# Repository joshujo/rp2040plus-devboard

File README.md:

# RP2040+ Devboard

This is a devboard that is designed to have a basic sensor, OLED screen, buttons and LEDs pre-embedded onto the board. The idea of this design was to have some basic hardware already available on the development board itself so an external bread board and some additional components with a kit and such is not needed to use it. Additionally, it can be used as a simple console or just a temperature monitor if desired. The board is designed to be extended with an additional 17 GPIO pins exposed to the user for prototyping. 

## Features

- 17 GPIO pins exposed
- HDC1080 accurate temperature + humidity sensor
- Buzzer
- OLED screen
- USB-C connector for power + data
- An additional power only USB-C connector designed to have an external battery plugged in
- 10 NeoPixel LEDs
- Programmable matrix buttons
- Up to 900mA +3V3
- Up to 3A VBUS
- 13 programmable buttons
- Designed to be used as is, no external bread board or components needed
- Moderate form factor of 100x40mm
- RP2040 comes with another I²C bus for more external components

# Datasheet

## Base
HDC1080 Addr: 1000000\
OLED Addr: 0111100 or 0111101\
Buzzer: GPIO24\
LED: GPIO25\
Neopixels: GPIO14

## Keypad
Shift: GPIO13\
ROW0: GPIO15\
ROW1: GPIO16\
ROW2: GPIO17\
ROW3: GPIO18\
COL0: GPIO19\
COL1: GPIO20\
COL2: GPIO21

## I²C
SDA: GPIO22\
SCL: GPIO23

# Schematic

# PCB

# BOM

| Item                     | Description                                                                                                                   | Quantity(For 5 units at minimum order amount) | Unit Price | Total Price | URL                                                                                                      | Running Total |
| ------------------------ | ----------------------------------------------------------------------------------------------------------------------------- | --------------------------------------------- | ---------- | ----------- | -------------------------------------------------------------------------------------------------------- | ------------- |
| CL05A105KP5NNNC          | 10V 1uF X5R ±10% 0402 Ceramic Capacitors RoHS                                                                                 | 100                                           | 0.0017     | $0.17       | [https://www.lcsc.com/product-detail/C14445.html](https://www.lcsc.com/product-detail/C14445.html)       | $0.17         |
| CL05B104KO5NNNC          | 16V 100nF X7R ±10% 0402 Ceramic Capacitors RoHS                                                                               | 100                                           | 0.0012     | $0.12       | [https://www.lcsc.com/product-detail/C1525.html](https://www.lcsc.com/product-detail/C1525.html)         | $0.29         |
| CC0603JRNPO9BN330        | 50V 33pF NP0 ±5% 0603 Ceramic Capacitors RoHS                                                                                 | 100                                           | 0.0024     | $0.24       | [https://www.lcsc.com/product-detail/C107047.html](https://www.lcsc.com/product-detail/C107047.html)     | $0.53         |
| CL10B104KB8NNNC          | 50V 100nF X7R ±10% 0603 Ceramic Capacitors RoHS                                                                               | 100                                           | 0.0026     | $0.26       | [https://www.lcsc.com/product-detail/C1591.html](https://www.lcsc.com/product-detail/C1591.html)         | $0.79         |
| CL10A106KP8NNNC          | 10V 10uF X5R ±10% 0603 Ceramic Capacitors RoHS                                                                                | 50                                            | 0.0058     | $0.29       | [https://www.lcsc.com/product-detail/C19702.html](https://www.lcsc.com/product-detail/C19702.html)       | $1.08         |
| CL10A105KB8NNNC          | 50V 1uF X5R ±10% 0603 Ceramic Capacitors RoHS                                                                                 | 50                                            | 0.0049     | $0.25       | [https://www.lcsc.com/product-detail/C15849.html](https://www.lcsc.com/product-detail/C15849.html)       | $1.33         |
| CL31A107MQHNNNE          | 6.3V 100uF X5R ±20% 1206 Ceramic Capacitors RoHS                                                                              | 20                                            | 0.0552     | $1.10       | [https://www.lcsc.com/product-detail/C15008.html](https://www.lcsc.com/product-detail/C15008.html)       | $2.43         |
| KT-0805B                 | 5mA 100mcd 460nm~475nm Blue 100mW 3.1V 0805 LED Indication - Discrete RoHS                                                    | 50                                            | 0.0117     | $0.59       | [https://www.lcsc.com/product-detail/C2293.html](https://www.lcsc.com/product-detail/C2293.html)         | $3.02         |
| CD4148WSP                | 1A 4ns Independent 75V 1.25V@100mA 150mA 0805 Single Diodes RoHS                                                              | 100                                           | 0.0118     | $1.18       | [https://www.lcsc.com/product-detail/C30584799.html](https://www.lcsc.com/product-detail/C30584799.html) | $4.20         |
| WS2812B-2020             | SMD,2.2x2mm LED Addressable, Specialty RoHS                                                                                   | 60                                            | 0.0658     | $3.95       | [https://www.lcsc.com/product-detail/C965555.html](https://www.lcsc.com/product-detail/C965555.html)     | $8.15         |
| TYPE-C-31-M-12           | 1 16P Type-C SMD USB, DVI, HDMI Connector Assemblies RoHS                                                                     | 5                                             | 0.1762     | $0.88       | [https://www.lcsc.com/product-detail/C165948.html](https://www.lcsc.com/product-detail/C165948.html)     | $9.03         |
| SKTDLHE010               | Without Bracket Rectangular Button No 3.9mm SPST SMD Tactile Switches RoHS                                                    | 10                                            | 0.1646     | $1.65       | [https://www.lcsc.com/product-detail/C380198.html](https://www.lcsc.com/product-detail/C380198.html)     | $10.68        |
| SKSLLBE010               | 12V 2.2mm Round Button No 4.5mm SPST 50mA SMD,4.5x2.2mm Tactile Switches RoHS                                                 | 65                                            | 0.159      | $10.34      | [https://www.lcsc.com/product-detail/C358617.html](https://www.lcsc.com/product-detail/C358617.html)     | $21.02        |
| RP2040                   | 133MHz 30 LQFN-56(7x7) Microcontrollers RoHS                                                                                  | 3                                             | 0.9482     | $2.84       | [https://www.lcsc.com/product-detail/C2040.html](https://www.lcsc.com/product-detail/C2040.html)         | $23.86        |
| HDC1080DMBR              | ±2%RH -40℃~+125℃ 0%RH~100%RH I2C WSON-6(3x3) Humidity, Moisture Sensors RoHS                                                  | 5                                             | 0.9001     | $4.50       | [https://www.lcsc.com/product-detail/C82227.html](https://www.lcsc.com/product-detail/C82227.html)       | $28.36        |
| NX3225GA-12MHZ-STD-CRG-2 | 8pF SMD3225-4P Crystals RoHS                                                                                                  | 5                                             | 0.257      | $1.29       | [https://www.lcsc.com/product-detail/C481407.html](https://www.lcsc.com/product-detail/C481407.html)     | $29.65        |
| MLT-8530                 | 80dB Passive (Externally Driven) 2.7kHz 3.6V Electromagnetic SMD,8.5x8.5mm Alarms, Buzzers, and Sirens RoHS                   | 5                                             | 0.1941     | $0.97       | [https://www.lcsc.com/product-detail/C94599.html](https://www.lcsc.com/product-detail/C94599.html)       | $30.62        |
| TPS2116DRLR              | 2 Active High 2.5A SOT-583 Power Distribution Switches, Load Drivers RoHS                                                     | 5                                             | 0.3756     | $1.88       | [https://www.lcsc.com/product-detail/C3235557.html](https://www.lcsc.com/product-detail/C3235557.html)   | $32.50        |
| HS96L03W2C03             | 0.96 128x64 SSD1315 I2C LCD, OLED, Graphic RoHS                                                                               | 5                                             | 2.0084     | $10.04      | [https://www.lcsc.com/product-detail/C5248080.html](https://www.lcsc.com/product-detail/C5248080.html)   | $42.54        |
| W25Q128JVSIQ             | 128Mbit 2.7V~3.6V 133MHz SPI SOIC-8-208mil Memory (ICs) RoHS                                                                  | 5                                             | 1.5657     | $7.83       | [https://www.lcsc.com/product-detail/C97521.html](https://www.lcsc.com/product-detail/C97521.html)       | $50.37        |
| NCP1117ST33T3G           | 62dB@(120Hz) Positive Fixed 3.3V SOT-223 Voltage Regulators - Linear, Low Drop Out (LDO) Regulators RoHS                      | 5                                             | 0.2315     | $1.16       | [https://www.lcsc.com/product-detail/C26537.html](https://www.lcsc.com/product-detail/C26537.html)       | $51.53        |
| BSS138LT1G               | 50V 200mA 225mW 5.6Ω@2.75V One N-channel SOT-23 Single FETs, MOSFETs RoHS                                                     | 20                                            | 0.0342     | $0.68       | [https://www.lcsc.com/product-detail/C82045.html](https://www.lcsc.com/product-detail/C82045.html)       | $52.21        |
| FRC0603F27R4TS           | 100mW 27.4Ω 75V ±100ppm/℃ Thick Film Resistor ±1% 0603 Chip Resistor - Surface Mount RoHS                                     | 100                                           | 0.0009     | $0.09       | [https://www.lcsc.com/product-detail/C5126244.html](https://www.lcsc.com/product-detail/C5126244.html)   | $52.30        |
| 0603WAF4700T5E           | 100mW 470Ω 75V ±100ppm/℃ Thick Film Resistor ±1% 0603 Chip Resistor - Surface Mount RoHS                                      | 100                                           | 0.0012     | $0.12       | [https://www.lcsc.com/product-detail/C23179.html](https://www.lcsc.com/product-detail/C23179.html)       | $52.42        |
| AR03BTCX5001             | 100mW 5kΩ 75V ±25ppm/℃ Thin Film Resistor ±0.1% 0603 Chip Resistor - Surface Mount RoHS                                       | 20                                            | 0.0302     | $0.60       | [https://www.lcsc.com/product-detail/C2828621.html](https://www.lcsc.com/product-detail/C2828621.html)   | $53.02        |
| RC0603FR-07100RL         | 100mW 100Ω 75V ±100ppm/℃ Thick Film Resistor ±1% 0603 Chip Resistor - Surface Mount RoHS                                      | 100                                           | 0.0011     | $0.11       | [https://www.lcsc.com/product-detail/C105588.html](https://www.lcsc.com/product-detail/C105588.html)     | $53.13        |
| FRC0603F5101TS           | 100mW 5.1kΩ 75V ±100ppm/℃ Thick Film Resistor ±1% 0603 Chip Resistor - Surface Mount RoHS                                     | 100                                           | 0.0009     | $0.09       | [https://www.lcsc.com/product-detail/C2907044.html](https://www.lcsc.com/product-detail/C2907044.html)   | $53.22        |
| RC0603FR-0710KL          | 100mW 10kΩ 75V ±100ppm/℃ Thick Film Resistor ±1% 0603 Chip Resistor - Surface Mount RoHS                                      | 100                                           | 0.0011     | $0.11       | [https://www.lcsc.com/product-detail/C98220.html](https://www.lcsc.com/product-detail/C98220.html)       | $53.33        |
| FRC0603F3302TS           | 33kΩ 100mW 75V ±100ppm/℃ Thick Film Resistor ±1% 0603 Chip Resistor - Surface Mount RoHS                                      | 100                                           | 0.0009     | $0.09       | [https://www.lcsc.com/product-detail/C2907028.html](https://www.lcsc.com/product-detail/C2907028.html)   | $53.42        |
| PZ254V-11-03P            | 3P 1x3P -40℃~+105℃ Pin Header Black 2.54mm 2.5mm 6mm 250V 3mm 1 3A Through Hole Through Hole,P=2.54mm Headers, Male Pins RoHS | 50                                            | 0.0162     | $0.81       | [https://www.lcsc.com/product-detail/C2937625.html](https://www.lcsc.com/product-detail/C2937625.html)   | $54.23        |
| PZ254V-11-04P            | 4P 1x4P -40℃~+105℃ Black Pin Header 2.54mm 2.5mm 6mm 250V 3mm 1 3A Through Hole Through Hole,P=2.54mm Headers, Male Pins RoHS | 20                                            | 0.0217     | $0.43       | [https://www.lcsc.com/product-detail/C2691448.html](https://www.lcsc.com/product-detail/C2691448.html)   | $54.66        |
| 0402WGF1001TCE           | 1kΩ 62.5mW 50V ±100ppm/℃ Thick Film Resistor ±1% 0402 Chip Resistor - Surface Mount RoHS                                      | 100                                           | 0.0006     | $0.06       | [https://www.lcsc.com/product-detail/C11702.html](https://www.lcsc.com/product-detail/C11702.html)       | $54.72        |
| KT-0805G                 | 5mA 430mcd 513nm\~528nm Emerald Green 100mW 2.6V\~3.1V 0805 LED Indication - Discrete RoHS                                      | 50                                            | 0.0112     | $0.56       | [https://www.lcsc.com/product-detail/C2297.html](https://www.lcsc.com/product-detail/C2297.html)         | $55.28        |
| TYPE-C 6P(073)           | 1 6P -25℃~+85℃ Type-C SMD USB, DVI, HDMI Connector Assemblies RoHS                                                            | 10                                            | 0.0357     | $0.36       | [https://www.lcsc.com/product-detail/C668623.html](https://www.lcsc.com/product-detail/C668623.html)     | $55.64        |

Plus $31.36 for the PCBs

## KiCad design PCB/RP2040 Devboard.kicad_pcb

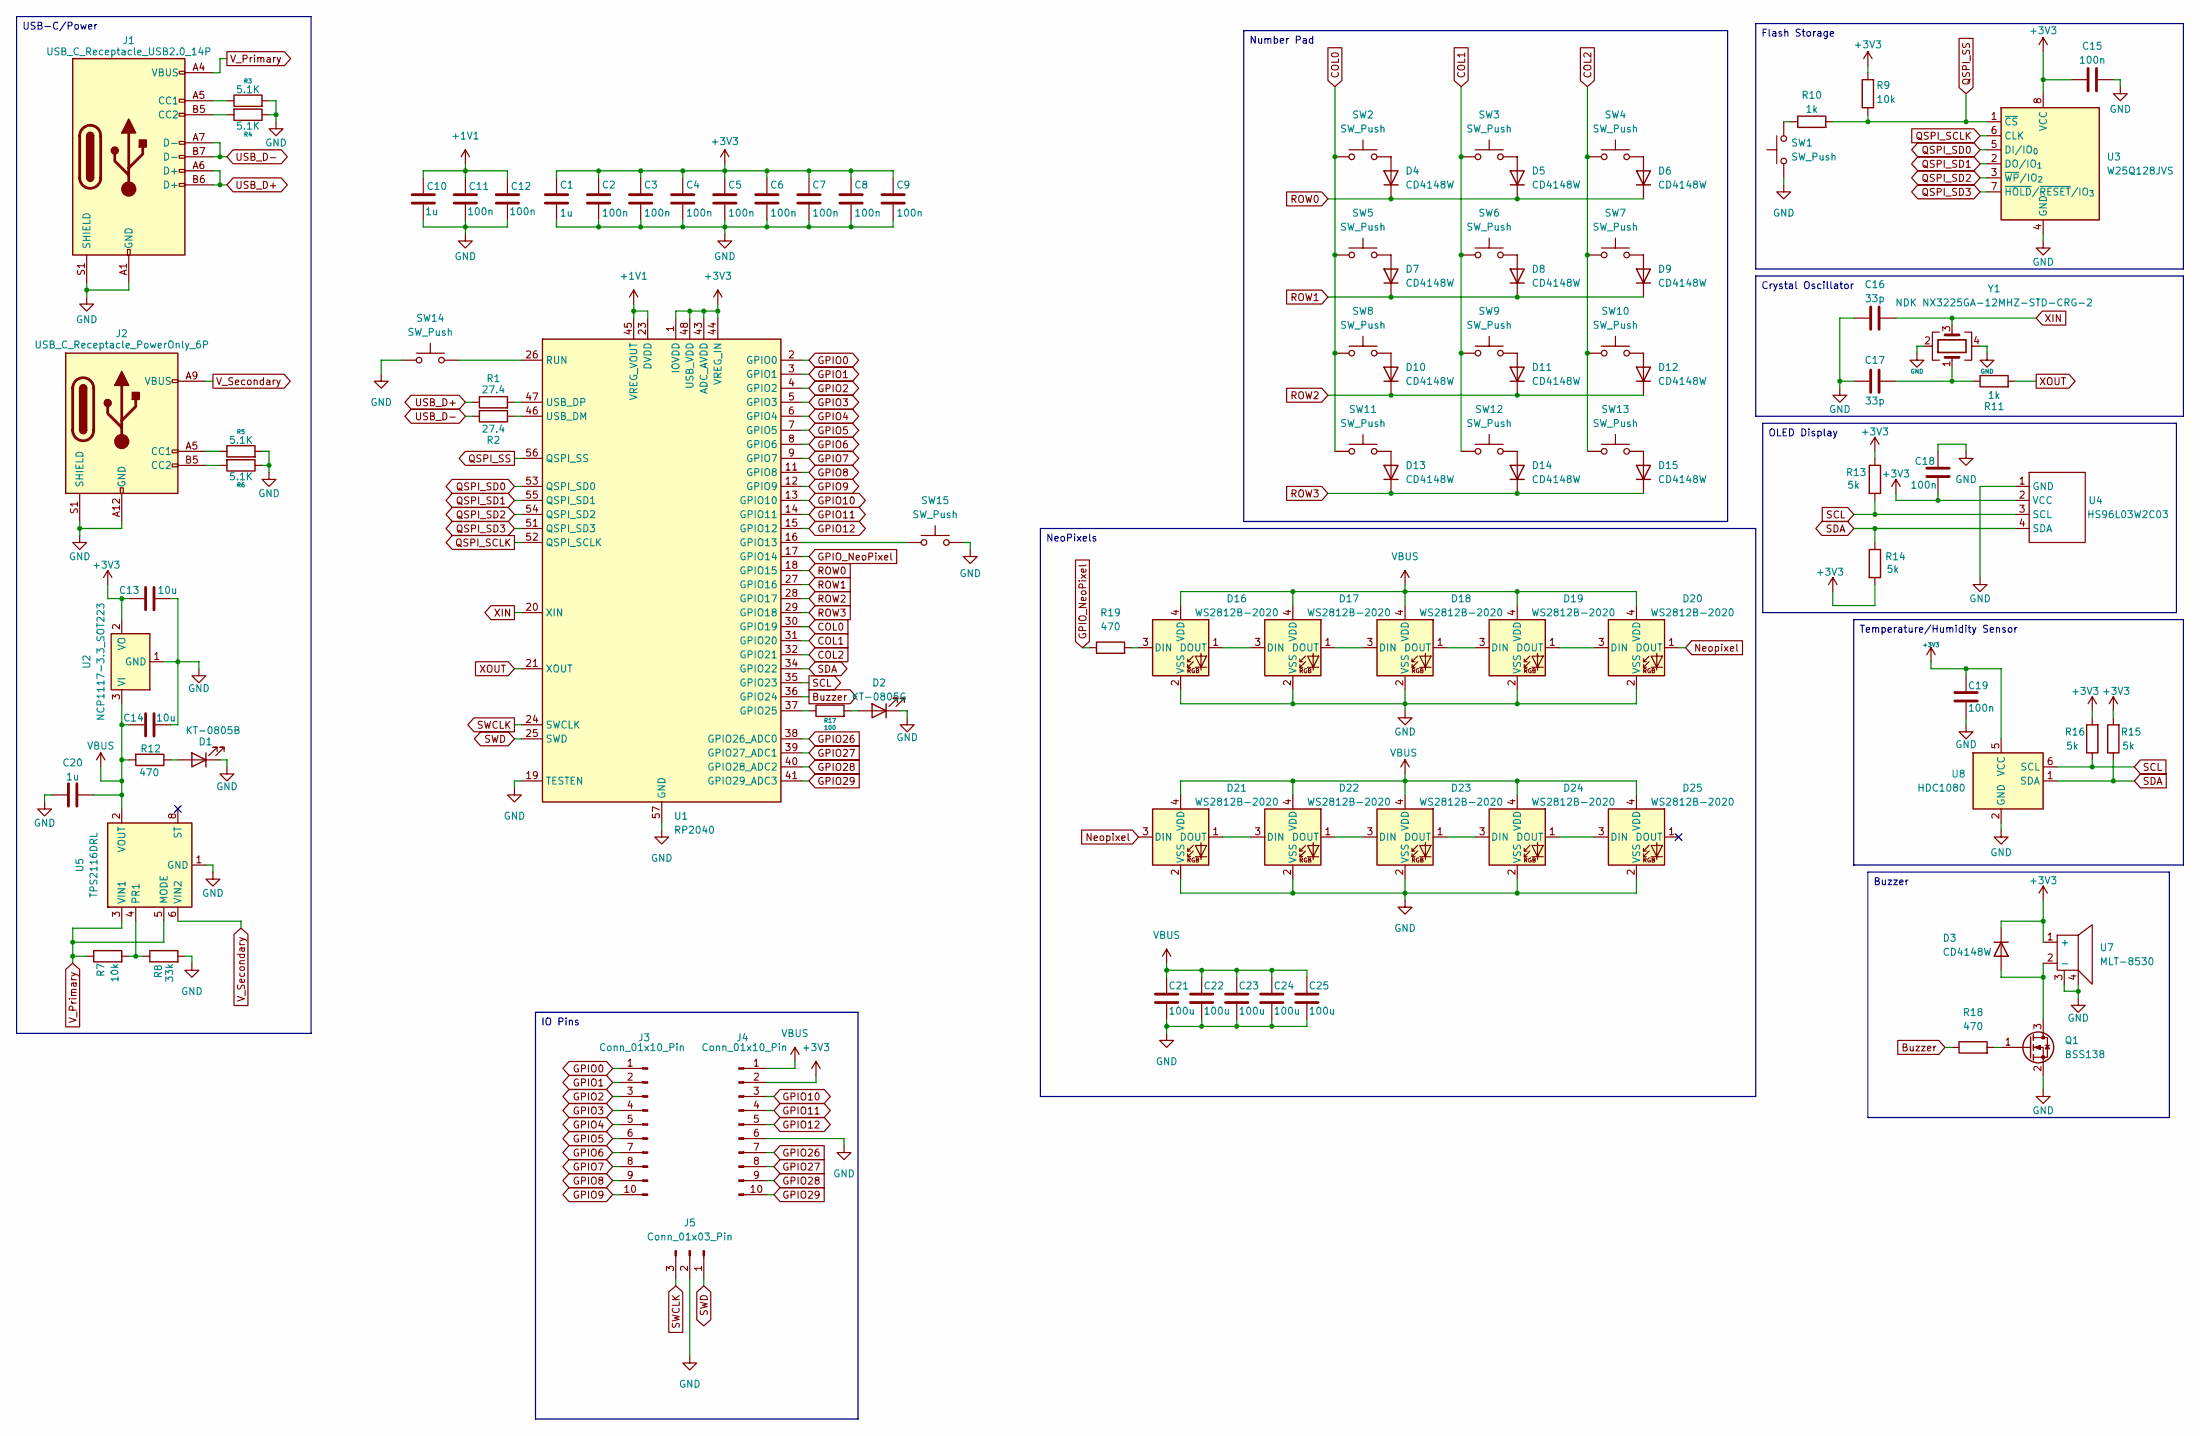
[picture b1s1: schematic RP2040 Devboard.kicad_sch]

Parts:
C1, C10: 1u; C_0402_1005Metric
C2, C3, C4, C5, C6, C7, C8, C9, C11, C12: 100n; C_0402_1005Metric
C13, C14: 10u; C_0603_1608Metric_Pad1.08x0.95mm_HandSolder
C15, C18, C19: 100n; C_0603_1608Metric_Pad1.08x0.95mm_HandSolder
C16, C17: 33p; C_0603_1608Metric_Pad1.08x0.95mm_HandSolder
C20: 1u; C_0603_1608Metric_Pad1.08x0.95mm_HandSolder
C21, C22, C23, C24, C25: 100u; C_1206_3216Metric_Pad1.33x1.80mm_HandSolder
D1: KT-0805B; LED_0805_2012Metric_Pad1.15x1.40mm_HandSolder
D2: KT-0805G; LED_0805_2012Metric_Pad1.15x1.40mm_HandSolder
D3, D4, D5, D6, D7, D8, D9, D10, D11, D12, D13, D14, D15: CD4148W; D_0805_2012Metric_Pad1.15x1.40mm_HandSolder
D16, D17, D18, D19, D20, D21, D22, D23, D24, D25: WS2812B-2020; LED_WS2812B-2020_PLCC4_2.0x2.0mm
J1: USB_C_Receptacle_USB2.0_14P; USB_C_Receptacle_G-Switch_GT-USB-7010ASV
J2: USB_C_Receptacle_PowerOnly_6P; USB_C_Receptacle_GCT_USB4125-xx-x_6P_TopMnt_Horizontal
J3, J4: Conn_01x10_Pin; PinHeader_1x10_P2.54mm_Vertical
J5: Conn_01x03_Pin; PinHeader_1x03_P2.54mm_Vertical
Q1: BSS138; SOT-23
R1, R2: 27.4; R_0603_1608Metric_Pad0.98x0.95mm_HandSolder
R3, R4, R5, R6: 5.1K; R_0603_1608Metric_Pad0.98x0.95mm_HandSolder
R7, R9: 10k; R_0603_1608Metric_Pad0.98x0.95mm_HandSolder
R8: 33k; R_0603_1608Metric_Pad0.98x0.95mm_HandSolder
R10: 1k; R_0603_1608Metric_Pad0.98x0.95mm_HandSolder
R11: 1k; R_0402_1005Metric
R12, R18, R19: 470; R_0603_1608Metric_Pad0.98x0.95mm_HandSolder
R13, R14, R15, R16: 5k; R_0603_1608Metric_Pad0.98x0.95mm_HandSolder
R17: 100; R_0603_1608Metric_Pad0.98x0.95mm_HandSolder
SW1, SW2, SW3, SW4, SW5, SW6, SW7, SW8, SW9, SW10, SW11, SW12, SW13, SW14, SW15: SW_Push; SW_Push_SPST_NO_Alps_SKRK
U1: RP2040; QFN-56-1EP_7x7mm_P0.4mm_EP3.2x3.2mm
U2: NCP1117-3.3_SOT223; SOT-223-3_TabPin2
U3: W25Q128JVS; SOIC-8_5.3x5.3mm_P1.27mm
U4: HS96L03W2C03
U5: TPS2116DRL; SOT-583-8
U7: MLT-8530
U8: HDC1080; Texas_S-PWSON-N6-HDC2080
Y1: NDK NX3225GA-12MHZ-STD-CRG-2; Crystal_SMD_3225-4Pin_3.2x2.5mm_HandSoldering

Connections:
+1V1: C10.1, C11.1, C12.1, U1.23 (DVDD), U1.45 (VREG_VOUT), U1.50 (DVDD)
+3V3: C1.1, C2.1, C3.1, C4.1, C5.1, C6.1, C7.1, C8.1, C9.1, C13.1, C15.1, C18.2, C19.1, D3.1 (K), J4.2, R9.2, R13.1, R14.2, R15.2, R16.2, U1.1 (IOVDD), U1.10 (IOVDD), U1.22 (IOVDD), U1.33 (IOVDD), U1.42 (IOVDD), U1.43 (ADC_AVDD), U1.44 (VREG_IN), U1.48 (USB_VDD), U1.49 (IOVDD), U2.2 (VO), U3.8 (VCC), U4.2 (VCC), U7.1 (+), U8.5 (VCC)
Buzzer: R18.1, U1.36 (GPIO24)
COL0: SW2.1, SW5.1, SW8.1, SW11.1, U1.30 (GPIO19)
COL1: SW3.1, SW6.1, SW9.1, SW12.1, U1.31 (GPIO20)
COL2: SW4.1, SW7.1, SW10.1, SW13.1, U1.32 (GPIO21)
GND: C1.2, C2.2, C3.2, C4.2, C5.2, C6.2, C7.2, C8.2, C9.2, C10.2, C11.2, C12.2, C13.2, C14.2, C15.2, C16.1, C17.2, C18.1, C19.2, C20.1, C21.2, C22.2, C23.2, C24.2, C25.2, D1.1 (K), D2.1 (K), D16.2 (VSS), D17.2 (VSS), D18.2 (VSS), D19.2 (VSS), D20.2 (VSS), D21.2 (VSS), D22.2 (VSS), D23.2 (VSS), D24.2 (VSS), D25.2 (VSS), J1.A1 (GND), J1.A12 (GND), J1.B1 (GND), J1.B12 (GND), J1.S1 (SHIELD), J2.A12 (GND), J2.B12 (GND), J2.S1 (SHIELD), J4.6, J5.2, Q1.2 (S), R3.2, R4.1, R5.2, R6.1, R8.2, SW1.1, SW14.1, SW15.2, U1.19 (TESTEN), U1.57 (GND), U2.1 (GND), U3.4 (GND), U4.1 (GND), U5.1 (GND), U7.3, U7.4, U8.2 (GND), Y1.2, Y1.4
GPIO0: J3.1, U1.2 (GPIO0)
GPIO1: J3.2, U1.3 (GPIO1)
GPIO2: J3.3, U1.4 (GPIO2)
GPIO3: J3.4, U1.5 (GPIO3)
GPIO4: J3.5, U1.6 (GPIO4)
GPIO5: J3.6, U1.7 (GPIO5)
GPIO6: J3.7, U1.8 (GPIO6)
GPIO7: J3.8, U1.9 (GPIO7)
GPIO8: J3.9, U1.11 (GPIO8)
GPIO9: J3.10, U1.12 (GPIO9)
GPIO10: J4.3, U1.13 (GPIO10)
GPIO11: J4.4, U1.14 (GPIO11)
GPIO12: J4.5, U1.15 (GPIO12)
GPIO26: J4.7, U1.38 (GPIO26_ADC0)
GPIO27: J4.8, U1.39 (GPIO27_ADC1)
GPIO28: J4.9, U1.40 (GPIO28_ADC2)
GPIO29: J4.10, U1.41 (GPIO29_ADC3)
GPIO_NeoPixel: R19.1, U1.17 (GPIO14)
Neopixel: D20.1 (DOUT), D21.3 (DIN)
unnamed: C17.1, R11.1, Y1.1
unnamed: D1.2 (A), R12.1
unnamed: D2.2 (A), R17.2
unnamed: D3.2 (A), Q1.3 (D), U7.2 (-)
unnamed: D4.2 (A), SW2.2
unnamed: D5.2 (A), SW3.2
unnamed: D6.2 (A), SW4.2
unnamed: D7.2 (A), SW5.2
unnamed: D8.2 (A), SW6.2
unnamed: D9.2 (A), SW7.2
unnamed: D10.2 (A), SW8.2
unnamed: D11.2 (A), SW9.2
unnamed: D12.2 (A), SW10.2
unnamed: D13.2 (A), SW11.2
unnamed: D14.2 (A), SW12.2
unnamed: D15.2 (A), SW13.2
unnamed: D16.3 (DIN), R19.2
unnamed: D16.1 (DOUT), D17.3 (DIN)
unnamed: D17.1 (DOUT), D18.3 (DIN)
unnamed: D18.1 (DOUT), D19.3 (DIN)
unnamed: D19.1 (DOUT), D20.3 (DIN)
unnamed: D21.1 (DOUT), D22.3 (DIN)
unnamed: D22.1 (DOUT), D23.3 (DIN)
unnamed: D23.1 (DOUT), D24.3 (DIN)
unnamed: D24.1 (DOUT), D25.3 (DIN)
unnamed: J1.A5 (CC1), R3.1
unnamed: J1.B5 (CC2), R4.2
unnamed: J2.A5 (CC1), R5.1
unnamed: J2.B5 (CC2), R6.2
unnamed: Q1.1 (G), R18.2
unnamed: R10.1, SW1.2
unnamed: SW15.1, U1.16 (GPIO13)
unnamed: R17.1, U1.37 (GPIO25)
unnamed: SW14.2, U1.26 (RUN)
unnamed: R2.1, U1.46 (USB_DM)
unnamed: R1.2, U1.47 (USB_DP)
unnamed: R7.2, R8.1, U5.4 (PR1)
QSPI_SCLK: U1.52 (QSPI_SCLK), U3.6 (CLK)
QSPI_SD0: U1.53 (QSPI_SD0), U3.5 (DI/IO_{0})
QSPI_SD1: U1.55 (QSPI_SD1), U3.2 (DO/IO_{1})
QSPI_SD2: U1.54 (QSPI_SD2), U3.3 (~WP/IO_{2})
QSPI_SD3: U1.51 (QSPI_SD3), U3.7 (~HOLD/~RESET/IO_{3})
QSPI_SS: R9.1, R10.2, U1.56 (QSPI_SS), U3.1 (~CS)
ROW0: D4.1 (K), D5.1 (K), D6.1 (K), U1.18 (GPIO15)
ROW1: D7.1 (K), D8.1 (K), D9.1 (K), U1.27 (GPIO16)
ROW2: D10.1 (K), D11.1 (K), D12.1 (K), U1.28 (GPIO17)
ROW3: D13.1 (K), D14.1 (K), D15.1 (K), U1.29 (GPIO18)
SCL: R13.2, R16.1, U1.35 (GPIO23), U4.3 (SCL), U8.6 (SCL)
SDA: R14.1, R15.1, U1.34 (GPIO22), U4.4 (SDA), U8.1 (SDA)
SWCLK: J5.3, U1.24 (SWCLK)
SWD: J5.1, U1.25 (SWD)
USB_D+: J1.A6 (D+), J1.B6 (D+), R1.1
USB_D-: J1.A7 (D-), J1.B7 (D-), R2.2
VBUS: C14.1, C20.2, C21.1, C22.1, C23.1, C24.1, C25.1, D16.4 (VDD), D17.4 (VDD), D18.4 (VDD), D19.4 (VDD), D20.4 (VDD), D21.4 (VDD), D22.4 (VDD), D23.4 (VDD), D24.4 (VDD), D25.4 (VDD), J4.1, R12.2, U2.3 (VI), U5.2 (VOUT), U5.7 (VOUT)
V_Primary: J1.A4 (VBUS), J1.A9 (VBUS), J1.B4 (VBUS), J1.B9 (VBUS), R7.1, U5.3 (VIN1), U5.5 (MODE)
V_Secondary: J2.A9 (VBUS), J2.B9 (VBUS), U5.6 (VIN2)
XIN: C16.2, U1.20 (XIN), Y1.3
XOUT: R11.2, U1.21 (XOUT)

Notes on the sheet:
NeoPixels
IO Pins
OLED Display
Number Pad
Crystal Oscillator
Buzzer
USB-C/Power
Temperature/Humidity Sensor
Flash Storage

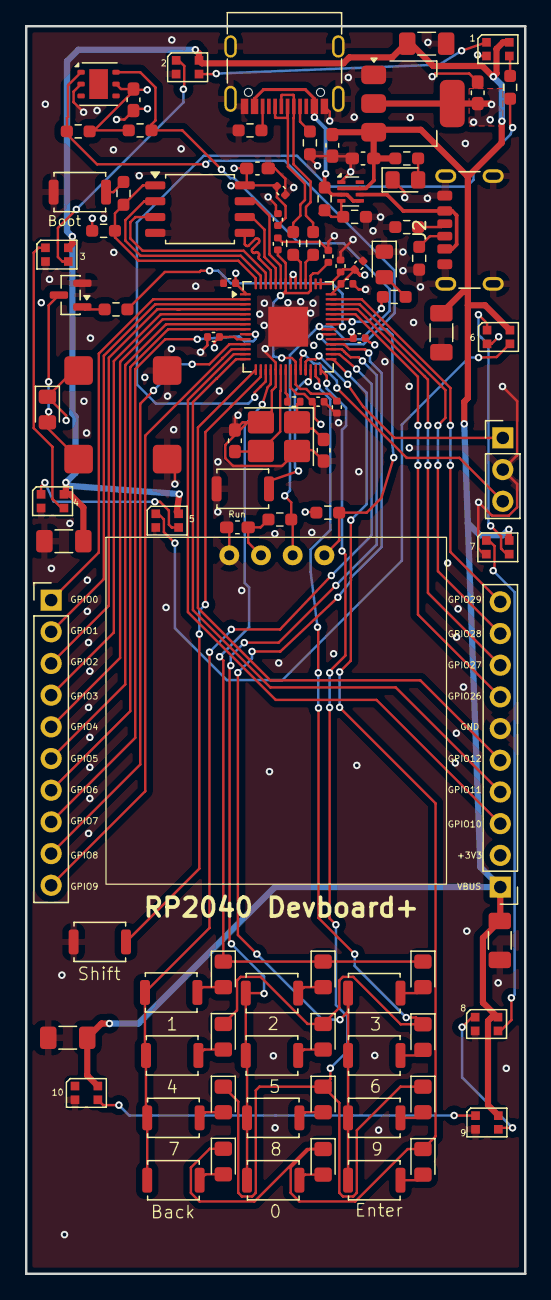
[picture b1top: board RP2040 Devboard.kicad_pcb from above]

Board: 4 copper layers, 40.0 x 100.0 mm, 98 parts (0 on the bottom side), 84 nets.

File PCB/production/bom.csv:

Designator,Footprint,Quantity,Value,LCSC Part #
"C1, C10",0402,2,1u,
"C11, C12, C2, C3, C4, C5, C6, C7, C8, C9",0402,10,100n,
"C13, C14",0603,2,10u,
"C15, C18, C19",0603,3,100n,
"C16, C17",0603,2,33p,
C20,0603,1,1u,
"C21, C22, C23, C24, C25",1206,5,100u,
"D1, D2",0805,2,KT-0805G,
"D10, D11, D12, D13, D14, D15, D3, D4, D5, D6, D7, D8, D9",0805,13,CD4148W,
"D16, D17, D18, D19, D20, D21, D22, D23, D24, D25",LED_WS2812B-2020_PLCC4_2.0x2.0mm,10,WS2812B-2020,
J1,USB_C_Receptacle_G-Switch_GT-USB-7010ASV,1,USB_C_Receptacle_USB2.0_14P,
J2,USB_C_Receptacle_GCT_USB4125-xx-x_6P_TopMnt_Horizontal,1,USB_C_Receptacle_PowerOnly_6P,
"J3, J4",PinHeader_1x10_P2.54mm_Vertical,2,Conn_01x10_Pin,
J5,PinHeader_1x03_P2.54mm_Vertical,1,Conn_01x03_Pin,
Q1,SOT-23,1,BSS138,
"R1, R2",0603,2,27.4,
R10,0603,1,1k,
R11,0402,1,1k,
"R12, R18, R19",0603,3,470,
"R13, R14, R15, R16",0603,4,5k,
R17,0603,1,100,
"R3, R4, R5, R6",0603,4,5.1K,
"R7, R9",0603,2,10k,
R8,0603,1,33k,
"SW1, SW10, SW11, SW12, SW13, SW14, SW15, SW2, SW3, SW4, SW5, SW6, SW7, SW8, SW9",SW_Push_SPST_NO_Alps_SKRK,15,SW_Push,
U1,QFN-56-1EP_7x7mm_P0.4mm_EP3.2x3.2mm,1,RP2040,
U2,SOT-223-3_TabPin2,1,NCP1117-3.3_SOT223,
U3,SOIC-8_5.3x5.3mm_P1.27mm,1,W25Q128JVS,
U4,HS96L03W2C03,1,HS96L03W2C03,
U5,SOT-583-8,1,TPS2116DRL,
U7,MLT-8530,1,MLT-8530,
U8,Texas_S-PWSON-N6-HDC2080,1,HDC1080,
Y1,Crystal_SMD_3225-4Pin_3.2x2.5mm_HandSoldering,1,NDK NX3225GA-12MHZ-STD-CRG-2,

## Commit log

2025-12-14 Added the necessary production files
2025-12-14 Added README.md
2025-12-14 Updated all the files and fixed any caught mistakes
2025-12-14 Fixed missing items in BOM
2025-12-14 Initial plan
2025-12-14 Complete comprehensive design review with documentation and fixes
